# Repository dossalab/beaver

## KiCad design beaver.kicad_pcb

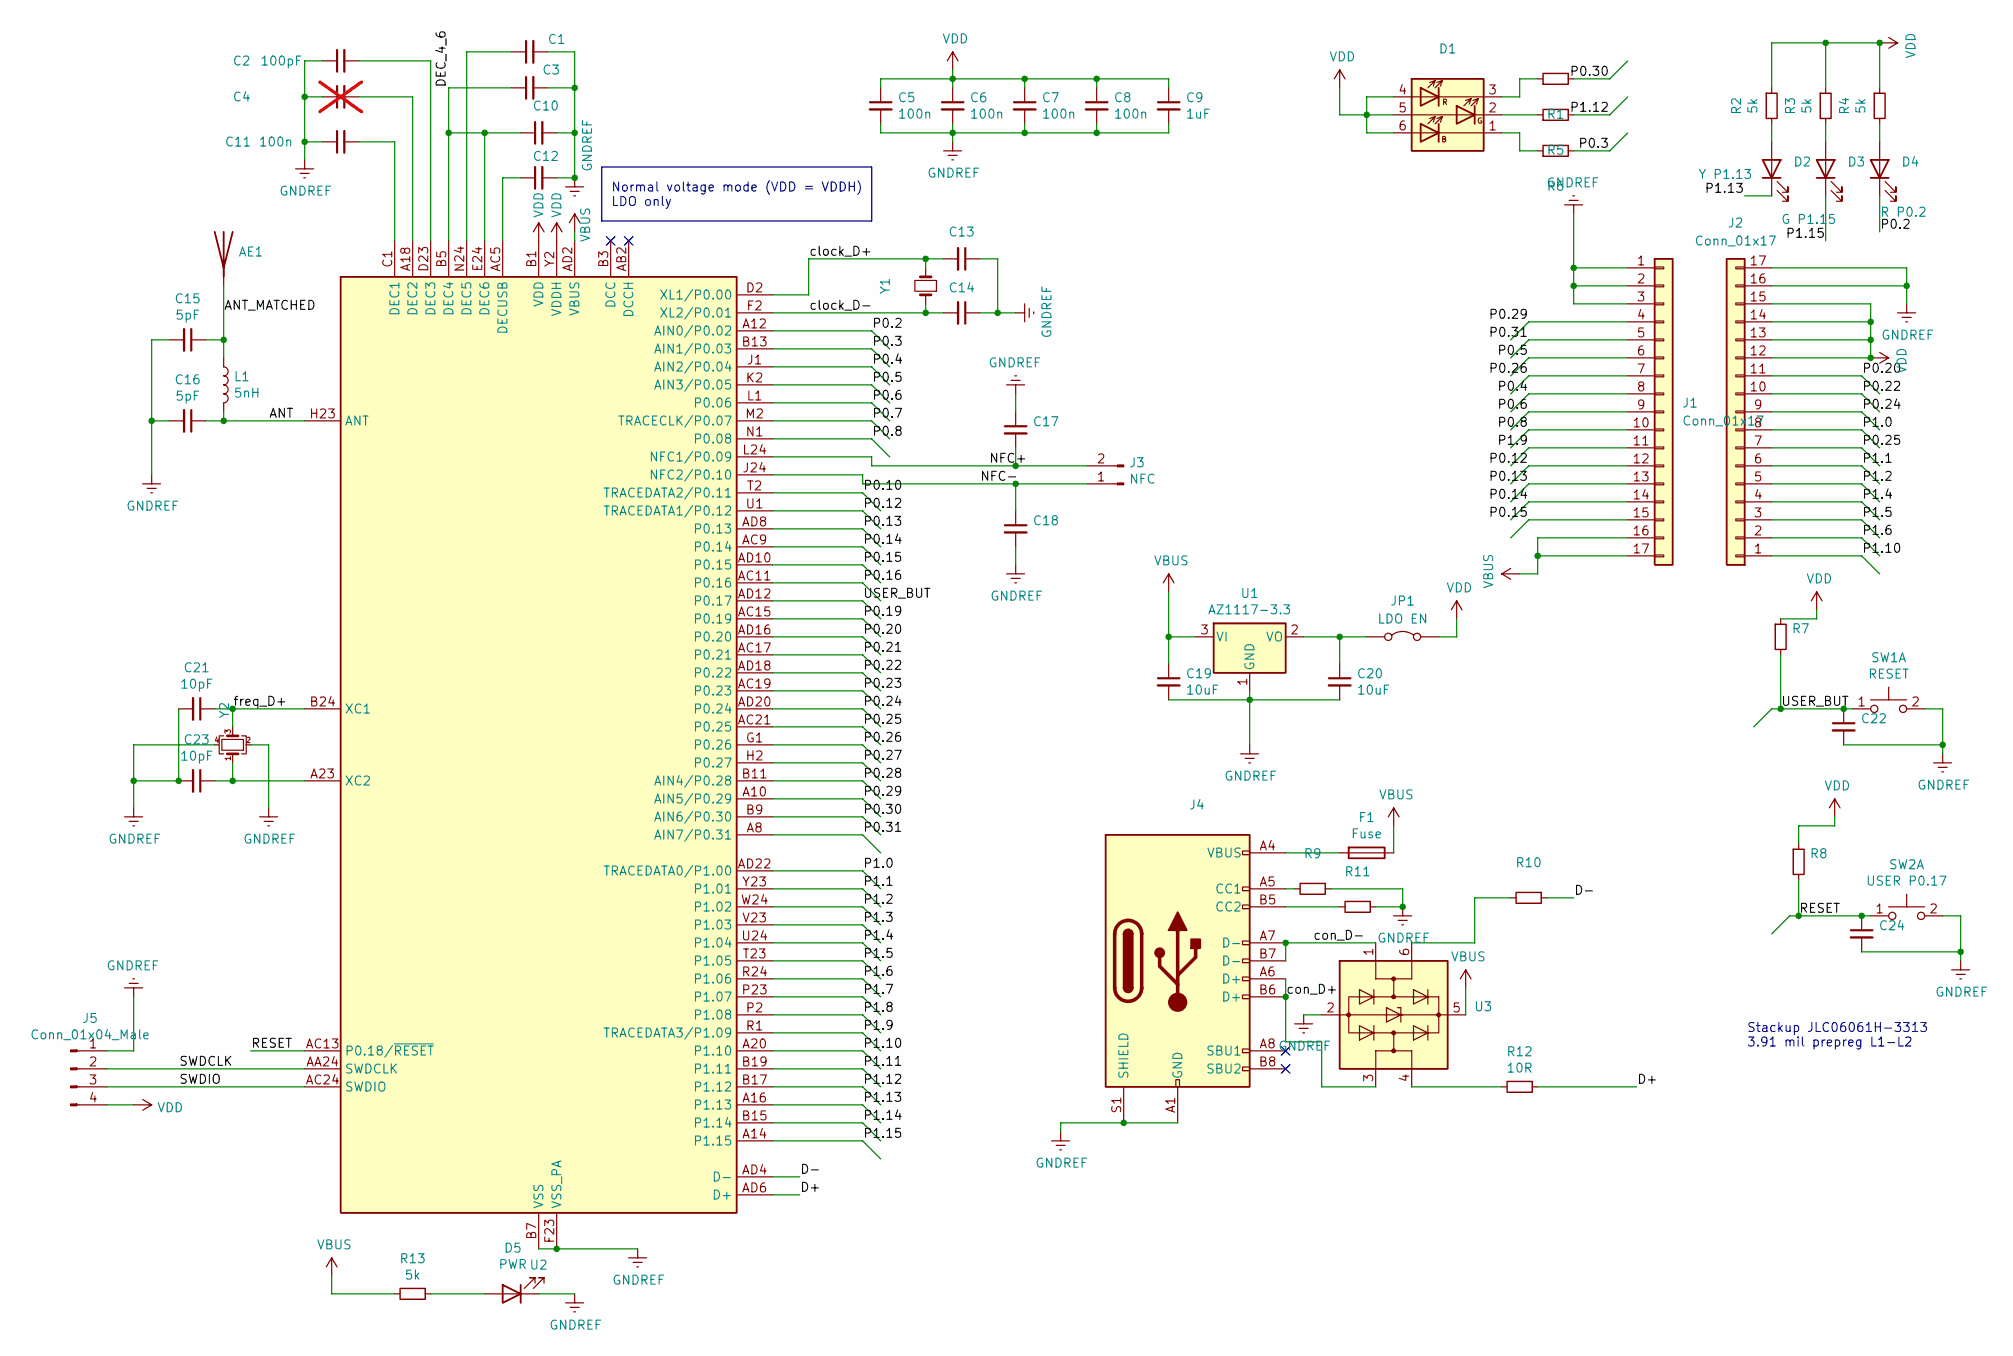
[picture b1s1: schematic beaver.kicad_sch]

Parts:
AE1: Antenna; U.FL_Hirose_U.FL-R-SMT-1_Vertical
C1: 820pF; C_0402_1005Metric
C2: 100pF; C_0402_1005Metric
C3: 100nF; C_0402_1005Metric
C4: 1uF; C_0402_1005Metric; not fitted
C5, C6, C7, C8, C11: 100n; C_0402_1005Metric
C9, C10, C12, C22, C24: 1uF; C_0402_1005Metric
C13, C14, C21, C23: 10pF; C_0402_1005Metric
C15, C16: 5pF; C_0402_1005Metric
C17, C18: 200pF; C_0402_1005Metric
C19, C20: 10uF; C_1206_3216Metric
D1: ASMT-YTC2-0AA02; LED_WS2812_PLCC6_5.0x5.0mm_P1.6mm
D2: Y P1.13; D_0603_1608Metric
D3: G P1.15; D_0603_1608Metric
D4: R P0.2; D_0603_1608Metric
D5: PWR; D_0603_1608Metric
F1: Fuse; Fuse_1206_3216Metric
J1, J2: Conn_01x17; PinHeader_1x17_P2.54mm_Vertical
J3: NFC; PinHeader_1x02_P2.54mm_Vertical
J4: USB_C_Receptacle_USB2.0; USB_C_Receptacle_XKB_U262-16XN-4BVC11
J5: Conn_01x04_Male; PinHeader_1x04_P2.54mm_Vertical
JP1: LDO EN; PinHeader_1x02_P2.54mm_Vertical
L1: 5nH; L_0402_1005Metric
R1, R2, R3, R4, R5, R6, R13: 5k; R_0603_1608Metric
R7, R8, R9, R11: 5k; R_0402_1005Metric
R10, R12: 10R; R_0402_1005Metric
SW1: RESET; SW_Push_1P1T_NO_CK_KSC6xxJ
SW2: USER P0.17; SW_Push_1P1T_NO_CK_KSC6xxJ
U1: AZ1117-3.3; SOT-223-3_TabPin2
U2: nRF52840; Nordic_AQFN-73-1EP_7x7mm_P0.5mm
U3: USBLC6-2SC6; SOT-23-6
Y1: Crystal_Small; Crystal_SMD_3215-2Pin_3.2x1.5mm
Y2: Crystal_GND24_Small; Crystal_SMD_2520-4Pin_2.5x2.0mm

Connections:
/ANT: C16.1, L1.2, U2.H23 (ANT)
/ANT_MATCHED: AE1.1 (A), C15.1, L1.1
/D+: R12.1, U2.AD6 (D+)
/D-: R10.1, U2.AD4 (D-)
/DEC_4_6: C3.1, C10.1, U2.B5 (DEC4), U2.E24 (DEC6)
/NFC+: C17.2, J3.2, U2.L24 (NFC1/P0.09)
/NFC-: C18.1, J3.1, U2.J24 (NFC2/P0.10)
/P0.2: D4.1 (K), U2.A12 (AIN0/P0.02)
/P0.3: R6.2, U2.B13 (AIN1/P0.03)
/P0.4: J1.8, U2.J1 (AIN2/P0.04)
/P0.5: J1.6, U2.K2 (AIN3/P0.05)
/P0.6: J1.9, U2.L1 (P0.06)
/P0.7: U2.M2 (TRACECLK/P0.07)
/P0.8: J1.10, U2.N1 (P0.08)
/P0.10: U2.T2 (TRACEDATA2/P0.11)
/P0.12: J1.12, U2.U1 (TRACEDATA1/P0.12)
/P0.13: J1.13, U2.AD8 (P0.13)
/P0.14: J1.14, U2.AC9 (P0.14)
/P0.15: J1.15, U2.AD10 (P0.15)
/P0.16: U2.AC11 (P0.16)
/P0.19: U2.AC15 (P0.19)
/P0.20: J2.11, U2.AD16 (P0.20)
/P0.21: U2.AC17 (P0.21)
/P0.22: J2.10, U2.AD18 (P0.22)
/P0.23: U2.AC19 (P0.23)
/P0.24: J2.9, U2.AD20 (P0.24)
/P0.25: J2.7, U2.AC21 (P0.25)
/P0.26: J1.7, U2.G1 (P0.26)
/P0.27: U2.H2 (P0.27)
/P0.28: U2.B11 (AIN4/P0.28)
/P0.29: J1.4, U2.A10 (AIN5/P0.29)
/P0.30: R1.2, U2.B9 (AIN6/P0.30)
/P0.31: J1.5, U2.A8 (AIN7/P0.31)
/P1.0: J2.8, U2.AD22 (TRACEDATA0/P1.00)
/P1.1: J2.6, U2.Y23 (P1.01)
/P1.2: J2.5, U2.W24 (P1.02)
/P1.3: U2.V23 (P1.03)
/P1.4: J2.4, U2.U24 (P1.04)
/P1.5: J2.3, U2.T23 (P1.05)
/P1.6: J2.2, U2.R24 (P1.06)
/P1.7: U2.P23 (P1.07)
/P1.8: U2.P2 (P1.08)
/P1.9: J1.11, U2.R1 (TRACEDATA3/P1.09)
/P1.10: J2.1, U2.A20 (P1.10)
/P1.11: U2.B19 (P1.11)
/P1.12: R5.2, U2.B17 (P1.12)
/P1.13: D2.1 (K), U2.A16 (P1.13)
/P1.14: U2.B15 (P1.14)
/P1.15: D3.1 (K), U2.A14 (P1.15)
/RESET: C24.1, R8.2, SW2.1 (C), U2.AC13 (P0.18/~RESET)
/SWDCLK: J5.2, U2.AA24 (SWDCLK)
/SWDIO: J5.3, U2.AC24 (SWDIO)
/USER_BUT: C22.1, R7.2, SW1.1 (C), U2.AD12 (P0.17)
/clock_D+: C13.2, U2.D2 (XL1/P0.00), Y1.2
/clock_D-: C14.2, U2.F2 (XL2/P0.01), Y1.1
/con_D+: J4.A6 (D+), J4.B6 (D+), U3.3 (I/O2)
/con_D-: J4.A7 (D-), J4.B7 (D-), U3.1 (I/O1)
/freq_D+: C21.1, U2.B24 (XC1), Y2.3
GNDREF: C1.2, C2.1, C3.2, C4.1, C5.2, C6.2, C7.2, C8.2, C9.2, C10.2, C11.1, C12.2, C13.1, C14.1, C15.2, C16.2, C17.1, C18.2, C19.2, C20.2, C21.2, C22.2, C23.2, C24.2, D5.1 (K), J1.1, J1.2, J1.3, J2.16, J2.17, J4.A1 (GND), J4.A12 (GND), J4.B1 (GND), J4.B12 (GND), J4.S1 (SHIELD), J5.1, R9.1, R11.1, SW1.2 (D), SW2.2 (D), U1.1 (GND), U2.B7 (VSS), U2.EP (VSS), U2.F23 (VSS_PA), U3.2 (GND), Y2.2, Y2.4
unnamed: D1.1 (KB), R6.1
unnamed: D1.2 (KG), R5.1
unnamed: D1.3 (KR), R1.1
unnamed: D2.2 (A), R2.2
unnamed: D3.2 (A), R3.2
unnamed: D4.2 (A), R4.2
unnamed: D5.2 (A), R13.1
unnamed: F1.2, J4.A4 (VBUS), J4.A9 (VBUS), J4.B4 (VBUS), J4.B9 (VBUS)
unnamed: J4.A5 (CC1), R9.2
unnamed: J4.B5 (CC2), R11.2
unnamed: C20.1, JP1.1 (A), U1.2 (VO)
unnamed: R10.2, U3.6 (I/O1)
unnamed: R12.2, U3.4 (I/O2)
unnamed: C11.2, U2.C1 (DEC1)
unnamed: C4.2, U2.A18 (DEC2)
unnamed: C2.2, U2.D23 (DEC3)
unnamed: C1.1, U2.N24 (DEC5)
unnamed: C12.1, U2.AC5 (DECUSB)
unnamed: C23.1, U2.A23 (XC2), Y2.1
VBUS: C19.1, F1.1, J1.16, J1.17, R13.2, U1.3 (VI), U2.AD2 (VBUS), U3.5 (VBUS)
VDD: C5.1, C6.1, C7.1, C8.1, C9.1, D1.4 (AR), D1.5 (AG), D1.6 (AB), J2.12, J2.13, J2.14, J2.15, J5.4, JP1.2 (B), R2.1, R3.1, R4.1, R7.1, R8.1, U2.A22 (VDD), U2.AD14 (VDD), U2.AD23 (VDD), U2.B1 (VDD), U2.W1 (VDD), U2.Y2 (VDDH)

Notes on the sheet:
Normal voltage mode (VDD = VDDH) LDO only
Stackup JLC06061H-3313 3.91 mil prepreg L1-L2

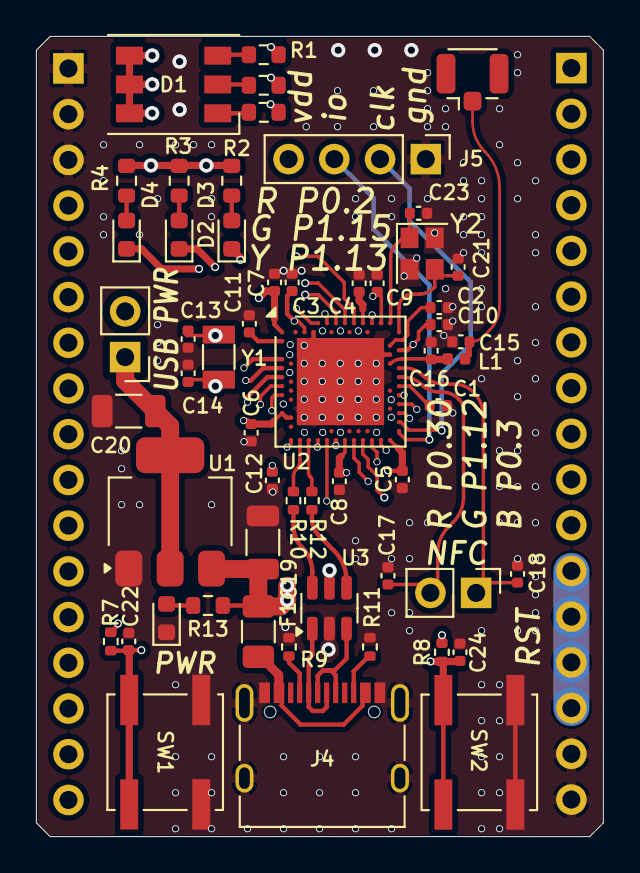
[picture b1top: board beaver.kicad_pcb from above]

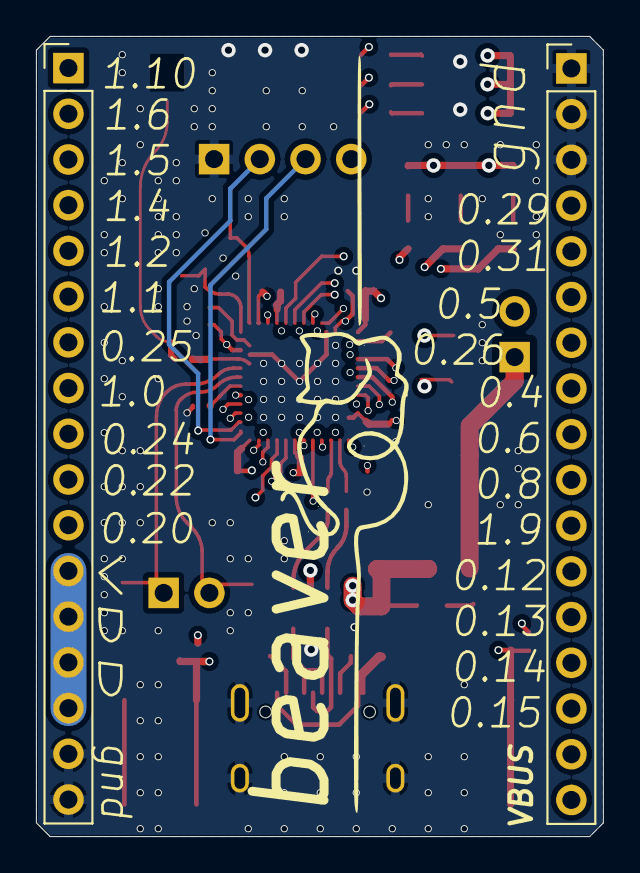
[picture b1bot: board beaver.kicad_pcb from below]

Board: 6 copper layers, 31.5 x 44.5 mm, 58 parts (2 on the bottom side), 67 nets.

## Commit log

2024-05-26 init commit
2024-05-27 final touches
2024-05-27 fix: rules due to fabric capabilities
2024-05-31 fix: 5V line connection, cat image, text placements, headers edge distanse
2024-05-31 pre-release preparations
2024-05-31 reroute the vsys
2024-05-31 switch stackup for cost measures
2024-06-12 switch to 6 layer stackup
2024-06-12 refill zones and plot
